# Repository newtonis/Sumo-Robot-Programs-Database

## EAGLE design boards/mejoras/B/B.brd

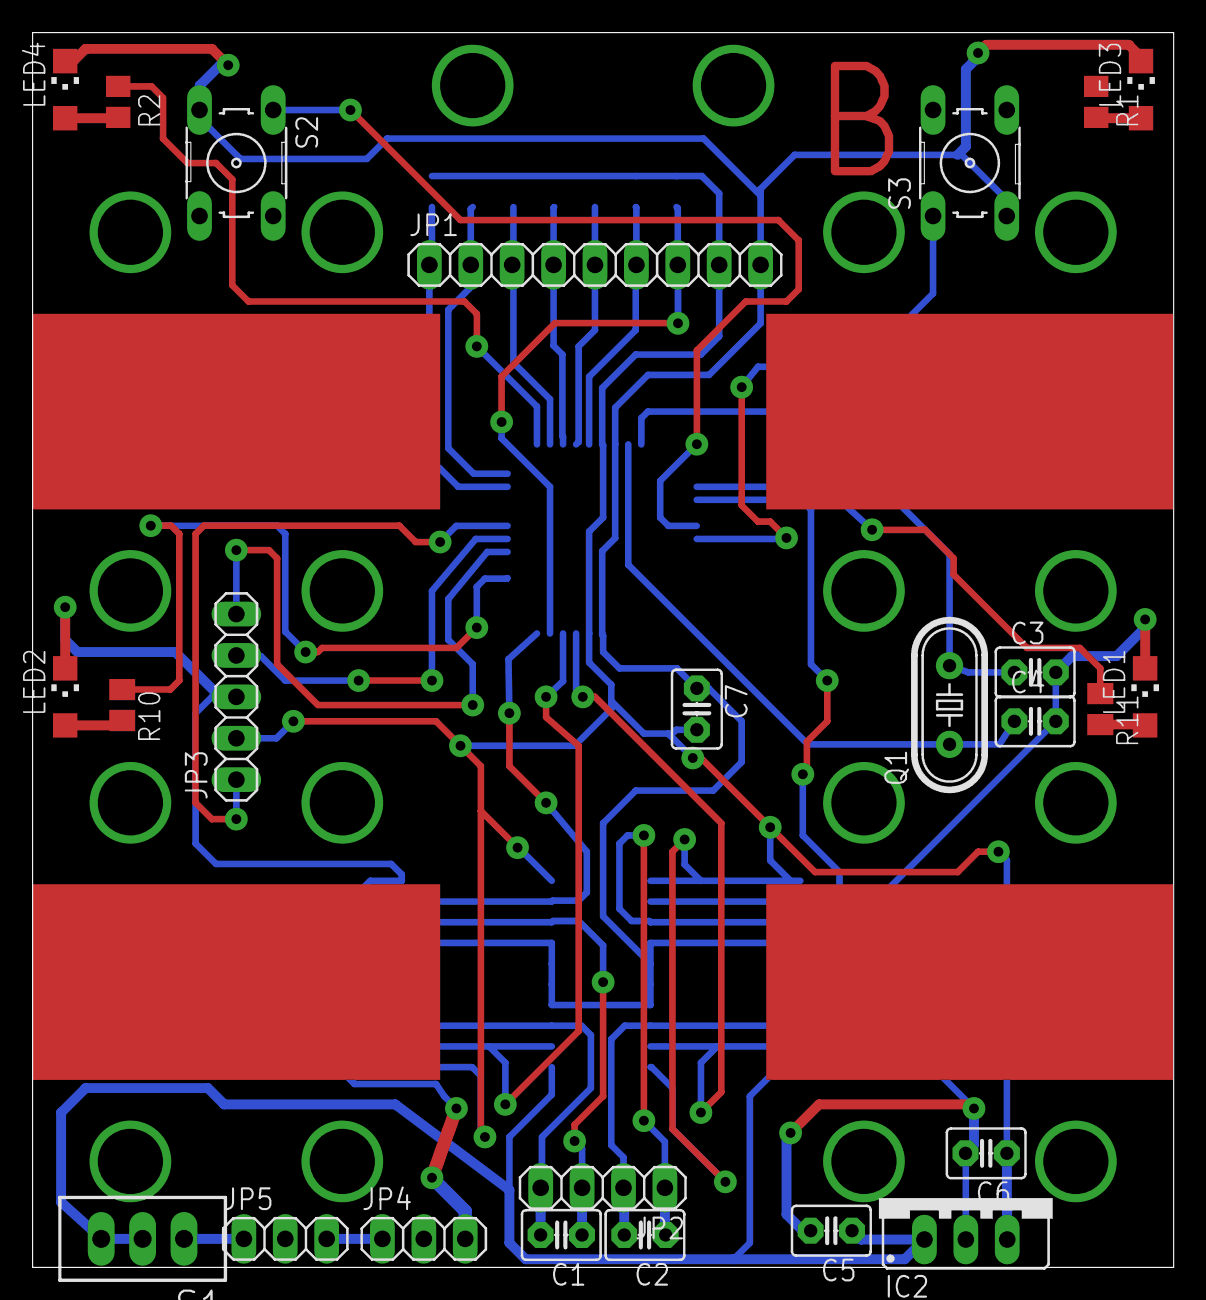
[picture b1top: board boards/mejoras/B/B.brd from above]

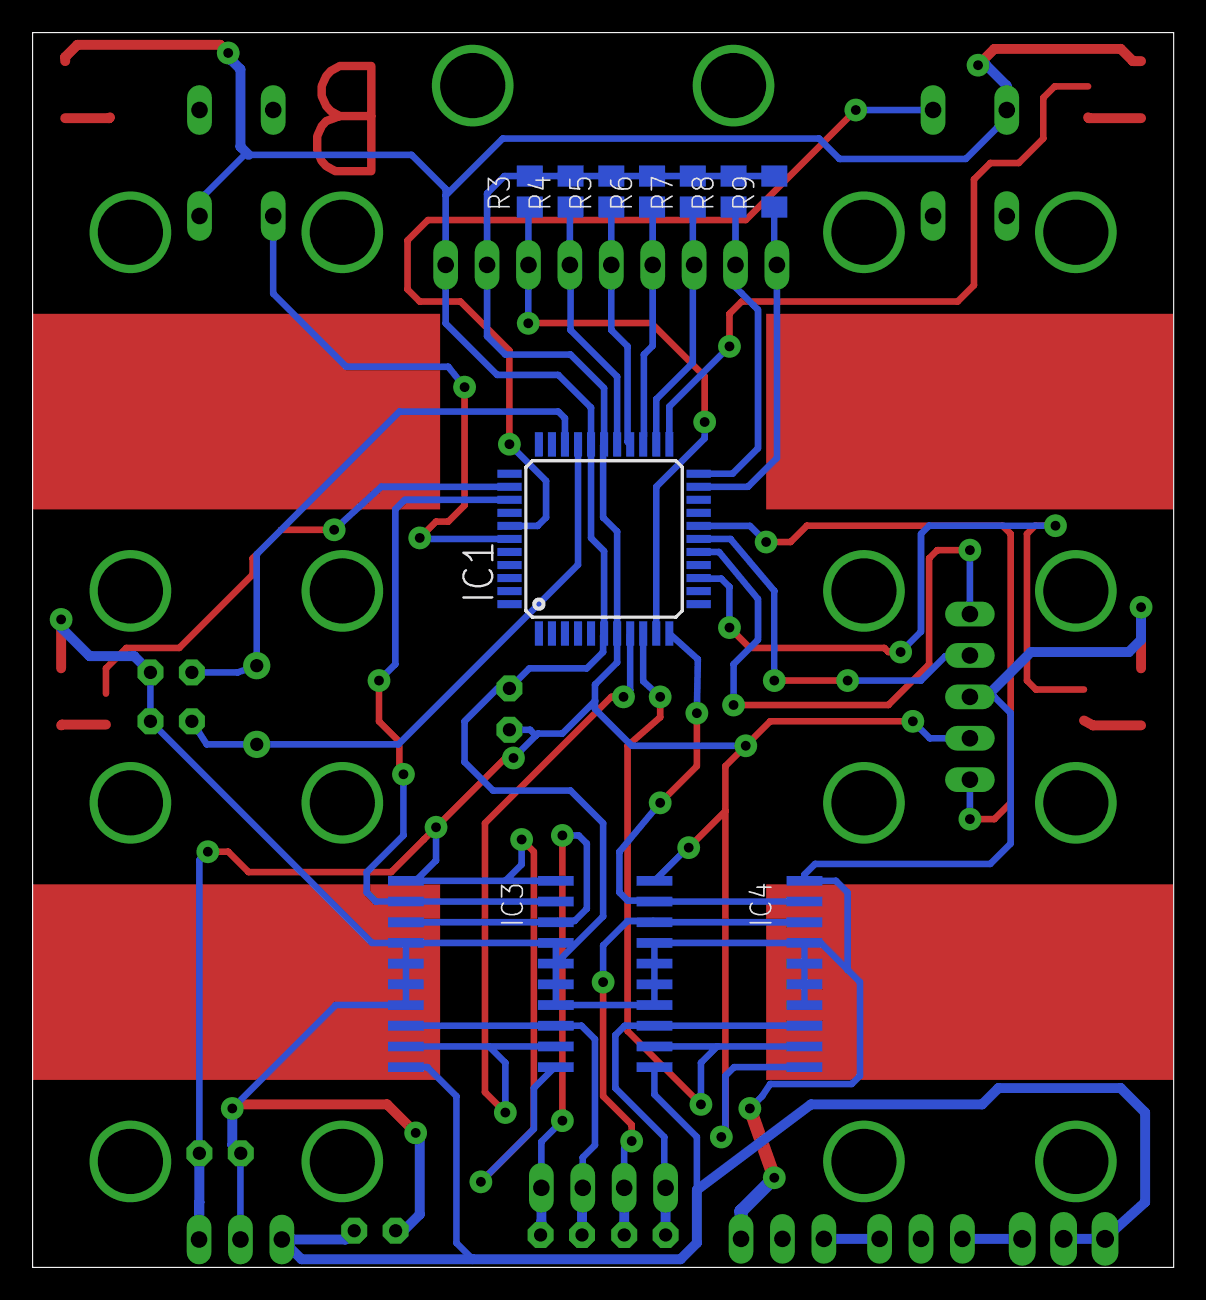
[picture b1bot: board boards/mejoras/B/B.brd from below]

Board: 2 copper layers, 70.0 x 75.8 mm, 35 parts (10 on the bottom side), 34 nets.

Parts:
C1, C2, C3, C4, C5, C6, C7: C2.5-3
IC1: PIC18F4455_TQFP; TQFP44
IC2: 78XXS
IC3, IC4: L293DD; SO20
JP1: 1X09
JP2: 1X04
JP3: 1X05
JP4, JP5: 1X03
LED1, LED2, LED3, LED4: CHIPLED_1206
Q1: HC49/S
R1, R2: R0805
R3, R4, R5, R6, R7, R8, R9, R10, R11: M0805
S1: TL39PO; TL3XPO
S2, S3: B3F-10XX

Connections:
5V: C6.1, C7.2, IC1.7, IC1.28, IC2.OUT, IC3.1, IC3.11, IC3.20, IC4.1, IC4.11, JP1.8, JP3.2, R3.2, R4.2, R5.2, R6.2, R7.2, R8.2, R9.2
B0: IC1.38, S2.1
B1: IC1.39, S3.1
GND: C3.2, C4.2, C5.2, C6.2, C7.1, IC1.6, IC1.29, IC2.GND, IC3.4, IC3.5, IC3.6, IC3.7, IC3.14, IC3.15, IC3.16, IC3.17, IC4.4, IC4.5, IC4.6, IC4.7, IC4.14, IC4.15, IC4.16, IC4.17, IC4.20, JP1.9, JP3.3, JP4.3, LED1.C, LED2.C, LED3.C, LED4.C, S2.3, S3.3
I1: IC1.36, IC3.2, IC3.19
I2: IC1.8, IC3.9, IC3.12
I3: IC1.11, IC4.2, IC4.19
I4: IC1.9, IC4.9, IC4.12
LED_A: IC1.14, R10.1
LED_B: IC1.35, R11.1
LED_D: IC1.23, R2.1
MCRL: IC1.18, JP3.1
unnamed: C4.1, IC1.30, Q1.1
unnamed: C3.1, IC1.31, Q1.2
unnamed: JP4.1, JP5.3
unnamed: LED2.A, R10.2
unnamed: LED1.A, R11.2
unnamed: LED3.A, R1.2
unnamed: LED4.A, R2.2
OUT1: C2.1, IC3.3, IC3.18, JP2.1
OUT2: C2.2, IC3.8, IC3.13, JP2.2
OUT3: C1.1, IC4.3, IC4.18, JP2.3
OUT4: C1.2, IC4.8, IC4.13, JP2.4
PGC: IC1.16, JP3.5
PGD: IC1.17, JP3.4
S0: IC1.21, JP1.1, R9.1
S1: IC1.22, JP1.2, R8.1
S2: IC1.24, JP1.3, R7.1
S3: IC1.25, JP1.4, R6.1
S4: IC1.26, JP1.5, R5.1
S5: IC1.27, JP1.6, R4.1
S6: IC1.10, JP1.7, R3.1
VPOWER: C5.1, IC2.IN, IC3.10, IC4.10, S1.2
VPREV: JP5.1, S1.1

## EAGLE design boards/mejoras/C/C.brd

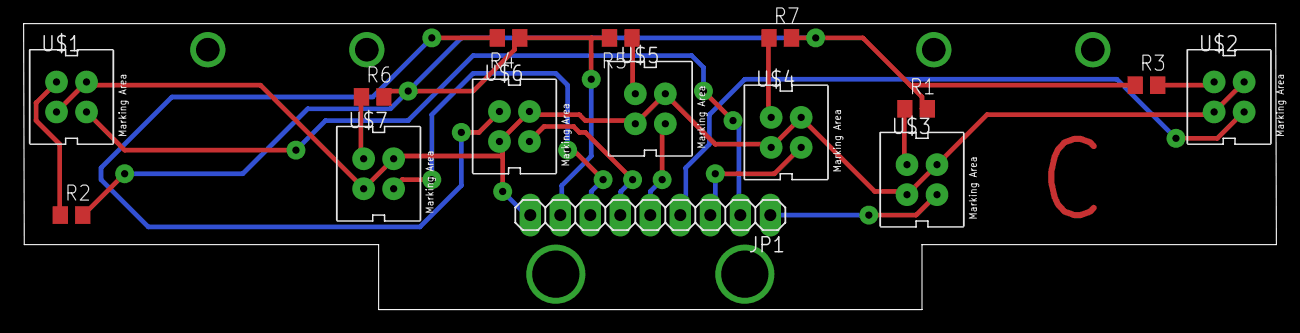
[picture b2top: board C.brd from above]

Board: 2 copper layers, 106.1 x 24.2 mm, 15 parts (0 on the bottom side), 16 nets.

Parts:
JP1: 1X09
R1, R2, R3, R4, R5, R6, R7: R0805
U$1, U$2, U$3, U$4, U$5, U$6, U$7: CNY70; 4

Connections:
5V: JP1.8, R1.2, R2.2, R3.1, R4.1, R5.2, R6.2, R7.2
GND: JP1.9, U$1.E, U$1.K, U$2.E, U$2.K, U$3.E, U$3.K, U$4.E, U$4.K, U$5.E, U$5.K, U$6.E, U$6.K, U$7.E, U$7.K
unnamed: R2.1, U$1.A
unnamed: R3.2, U$2.A
unnamed: R1.1, U$3.A
unnamed: R7.1, U$4.A
unnamed: R5.1, U$5.A
unnamed: R4.2, U$6.A
unnamed: R6.1, U$7.A
OUT0: JP1.1, U$3.C
OUT1: JP1.2, U$1.C
OUT2: JP1.3, U$4.C
OUT3: JP1.4, U$2.C
OUT4: JP1.5, U$5.C
OUT5: JP1.6, U$6.C
OUT6: JP1.7, U$7.C

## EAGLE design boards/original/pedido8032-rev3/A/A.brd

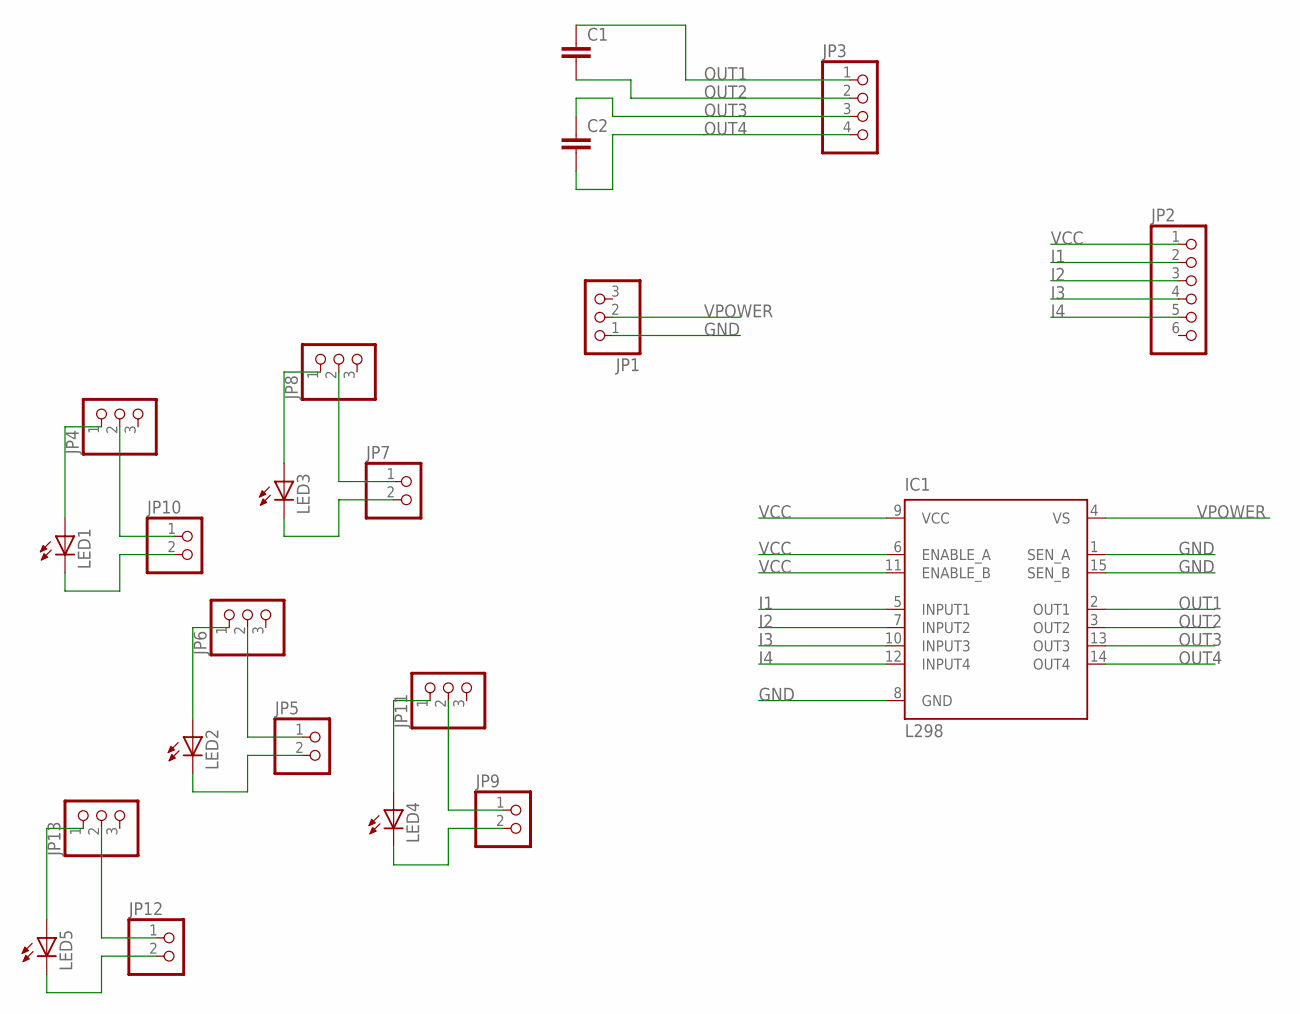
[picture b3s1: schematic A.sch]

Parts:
C1, C2: C2,5-3; C2.5-3
IC1: L298; MULTIWATT-15
JP1, JP4, JP6, JP8, JP11, JP13: PINHD-1X3; 1X03
JP2: PINHD-1X6; 1X06
JP3: PINHD-1X4; 1X04
JP5, JP7, JP9, JP10, JP12: PINHD-1X2; 1X02
LED1, LED2, LED3, LED4, LED5: LED5MM

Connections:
GND: IC1.1 (SEN_A), IC1.8 (GND), IC1.15 (SEN_B), JP1.1
I1: IC1.5 (INPUT1), JP2.2
I2: IC1.7 (INPUT2), JP2.3
I3: IC1.10 (INPUT3), JP2.4
I4: IC1.12 (INPUT4), JP2.5
unnamed: JP10.2, LED1.K (C)
unnamed: JP4.2, JP10.1
unnamed: JP4.1, LED1.A
unnamed: JP5.2, LED2.K (C)
unnamed: JP5.1, JP6.2
unnamed: JP6.1, LED2.A
unnamed: JP7.2, LED3.K (C)
unnamed: JP7.1, JP8.2
unnamed: JP8.1, LED3.A
unnamed: JP9.2, LED4.K (C)
unnamed: JP9.1, JP11.2
unnamed: JP11.1, LED4.A
unnamed: JP12.2, LED5.K (C)
unnamed: JP12.1, JP13.2
unnamed: JP13.1, LED5.A
OUT1: C1.1, IC1.2 (OUT1), JP3.1
OUT2: C1.2, IC1.3 (OUT2), JP3.2
OUT3: C2.1, IC1.13 (OUT3), JP3.3
OUT4: C2.2, IC1.14 (OUT4), JP3.4
VCC: IC1.6 (ENABLE_A), IC1.9 (VCC), IC1.11 (ENABLE_B), JP2.1
VPOWER: IC1.4 (VS), JP1.2

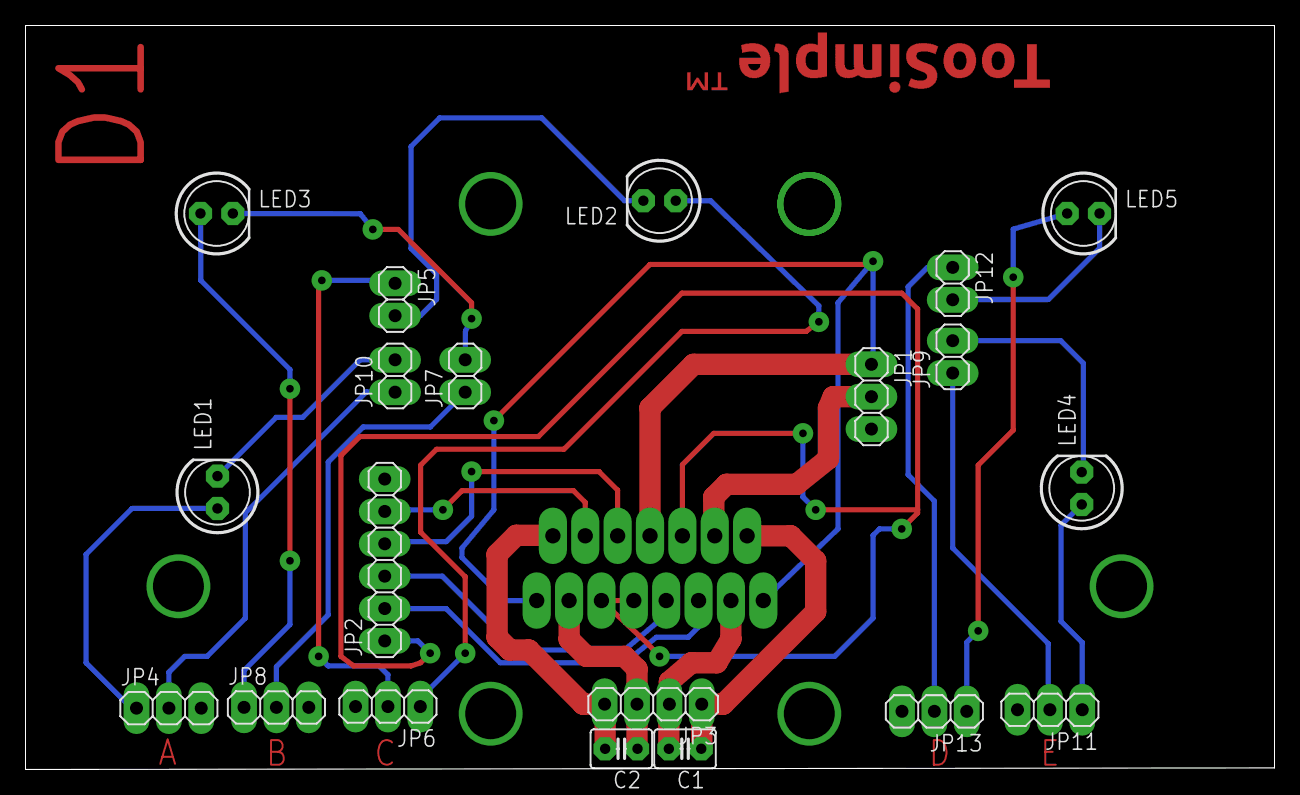
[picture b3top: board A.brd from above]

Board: 2 copper layers, 98.0 x 58.4 mm, 21 parts (1 on the bottom side), 26 nets.

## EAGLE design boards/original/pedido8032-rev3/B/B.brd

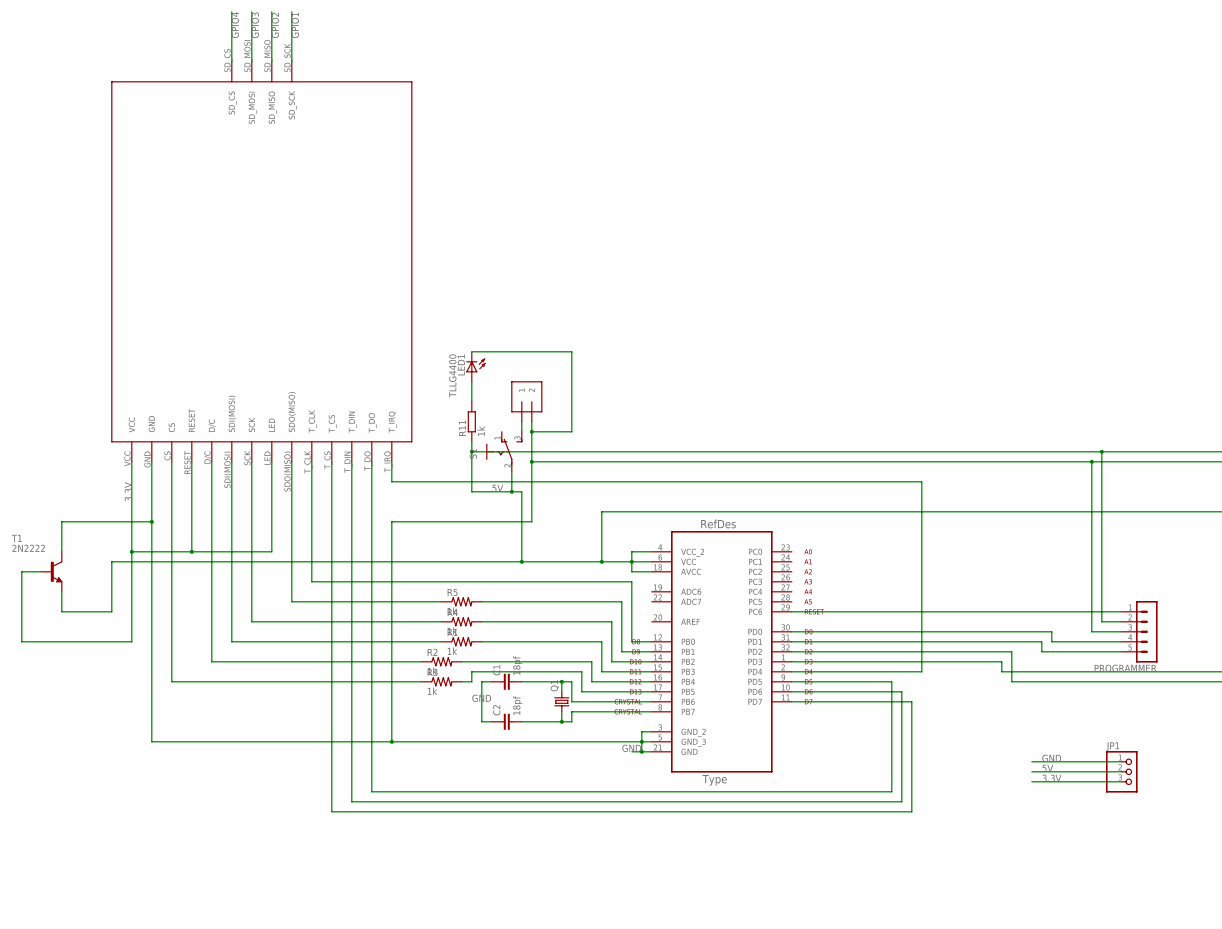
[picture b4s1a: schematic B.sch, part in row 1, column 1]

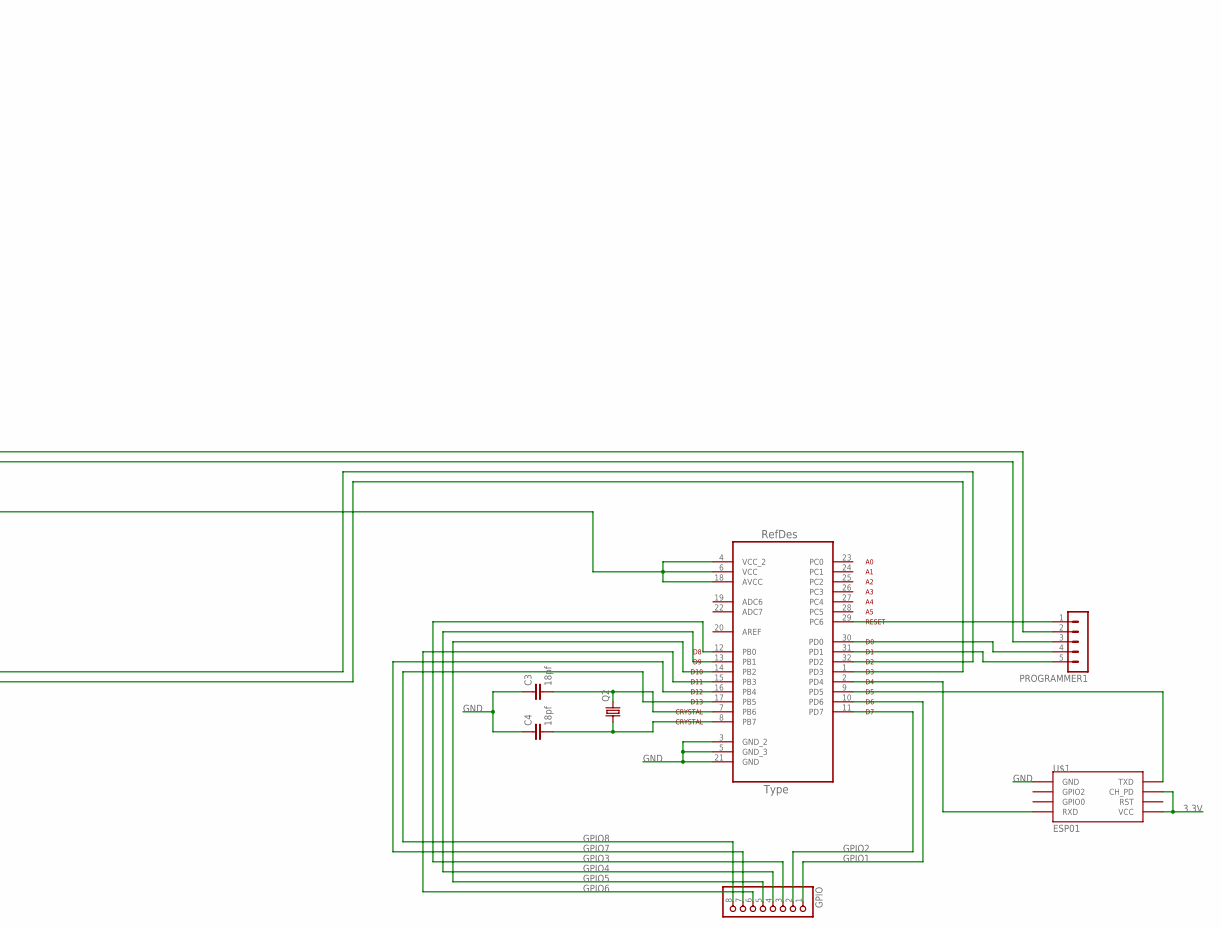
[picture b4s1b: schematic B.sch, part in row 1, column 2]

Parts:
C1, C2, C3, C4: 18pf; C2.5-3
DS2: DISPLAYSINATRA
GPIO: PINHD-1X8; 1X08
JP1: PINHD-1X3; 1X03
LED1: TLLG4400; LED3MM
POWER: 1X2-3.5MM
PROGRAMMER, PROGRAMMER1: MA05-1
Q1, Q2: CRYSTALHC49S; HC49/S
R1, R2, R3, R4, R5: 1k; R1206
R11: 1k; 0207/10
S1: 255SB
T1: 2N2222; TO92-EBC-OVAL
U1, U2: ATMEGA328P-AU; QFP80P900X900X120-32N
U$1: ESP01

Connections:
3.3V: DS2.LED, DS2.RESET, DS2.VCC, JP1.3, T1.B, U$1.CH_PD, U$1.VCC
5V: JP1.2, PROGRAMMER.2, PROGRAMMER1.2, R11.1, S1.2, T1.E, U1.4 (VCC_2), U1.6 (VCC), U1.18 (AVCC), U2.4 (VCC_2), U2.6 (VCC), U2.18 (AVCC)
GND: C1.1, C2.1, C3.1, C4.1, DS2.GND, JP1.1, LED1.K (C), POWER.2, PROGRAMMER.3, PROGRAMMER1.3, T1.C, U1.3 (GND_2), U1.5 (GND_3), U1.21 (GND), U2.3 (GND_2), U2.5 (GND_3), U2.21 (GND), U$1.GND
GPIO1: DS2.SD_SCK, GPIO.1, U2.10 (PD6)
GPIO2: DS2.SD_MISO, GPIO.2, U2.11 (PD7)
GPIO3: DS2.SD_MOSI, GPIO.3, U2.12 (PB0)
GPIO4: DS2.SD_CS, GPIO.4, U2.13 (PB1)
GPIO5: GPIO.5, U2.14 (PB2)
GPIO6: GPIO.6, U2.15 (PB3)
GPIO7: GPIO.7, U2.16 (PB4)
GPIO8: GPIO.8, U2.17 (PB5)
unnamed: C1.2, Q1.2, U1.7 (PB6)
unnamed: C2.2, Q1.1, U1.8 (PB7)
unnamed: R4.2, U1.14 (PB2)
unnamed: DS2.D/C, R2.1
unnamed: DS2.CS, R3.1
unnamed: DS2.SDI(MOSI), R1.1
unnamed: DS2.SCK, R4.1
unnamed: DS2.SDO(MISO), R5.1
unnamed: DS2.T_CLK, U1.12 (PB0)
unnamed: DS2.T_CS, U1.11 (PD7)
unnamed: DS2.T_DIN, U1.10 (PD6)
unnamed: PROGRAMMER1.1, U2.29 (PC6)
unnamed: DS2.T_DO, U1.9 (PD5)
unnamed: R1.2, U1.15 (PB3)
unnamed: R2.2, U1.16 (PB4)
unnamed: R3.2, U1.17 (PB5)
unnamed: R5.2, U1.13 (PB1)
unnamed: PROGRAMMER1.4, U2.30 (PD0)
unnamed: PROGRAMMER1.5, U2.31 (PD1)
unnamed: U1.1 (PD3), U2.32 (PD2)
unnamed: U1.32 (PD2), U2.1 (PD3)
unnamed: DS2.T_IRQ, U1.2 (PD4)
unnamed: U2.2 (PD4), U$1.RX (RXD)
unnamed: C3.2, Q2.2, U2.7 (PB6)
unnamed: C4.2, Q2.1, U2.8 (PB7)
unnamed: U2.9 (PD5), U$1.TX (TXD)
unnamed: PROGRAMMER.1, U1.29 (PC6)
unnamed: PROGRAMMER.4, U1.30 (PD0)
unnamed: PROGRAMMER.5, U1.31 (PD1)
unnamed: LED1.A, R11.2
unnamed: POWER.1, S1.3 (S)

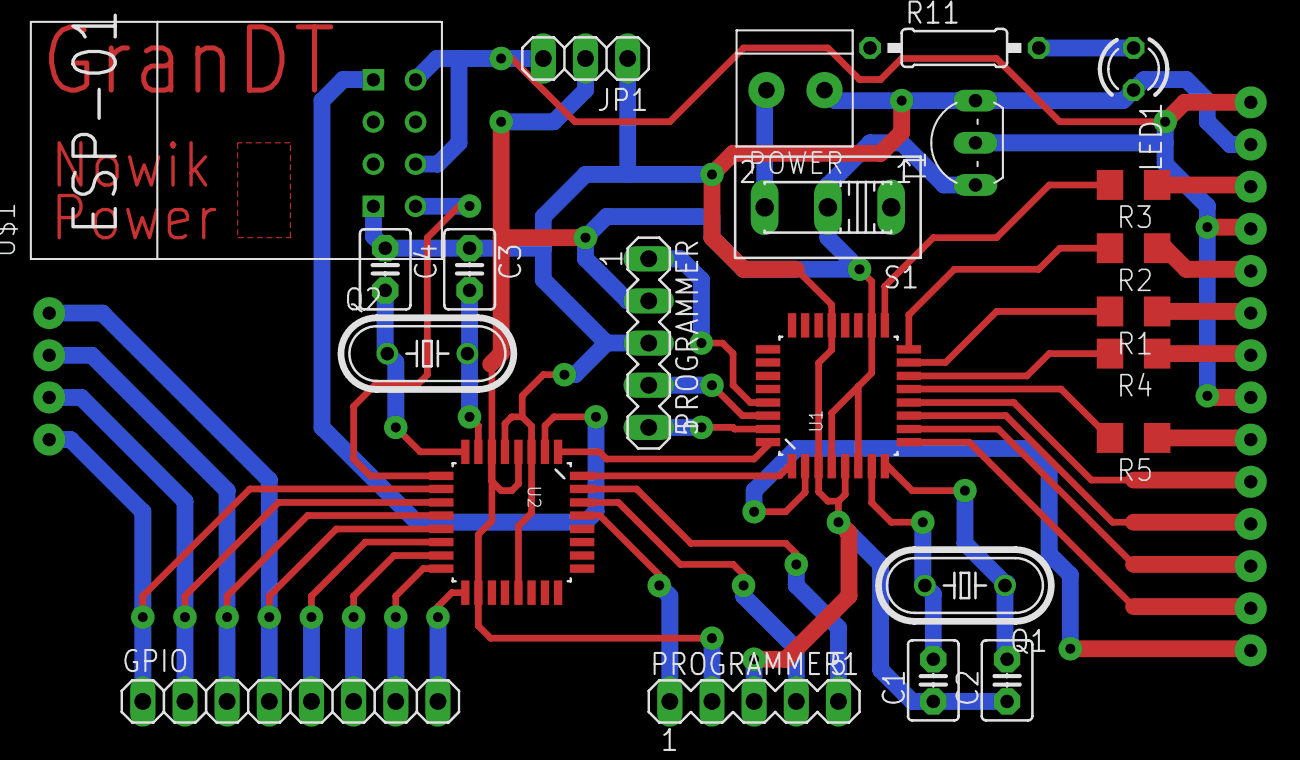
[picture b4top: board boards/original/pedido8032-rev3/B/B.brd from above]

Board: 2 copper layers, 24 parts (1 on the bottom side), 42 nets.
